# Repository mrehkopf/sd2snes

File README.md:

sd2snes
=======

SD card based multi-purpose cartridge for the SNES

See [FURiOUS's README](README.Savestates.FURiOUS.md) for information on Save States!

See [the USB protocol documentation](docs/usb-protocol.md) for the direct CDC
interface used by native clients and USB2SNES bridges.

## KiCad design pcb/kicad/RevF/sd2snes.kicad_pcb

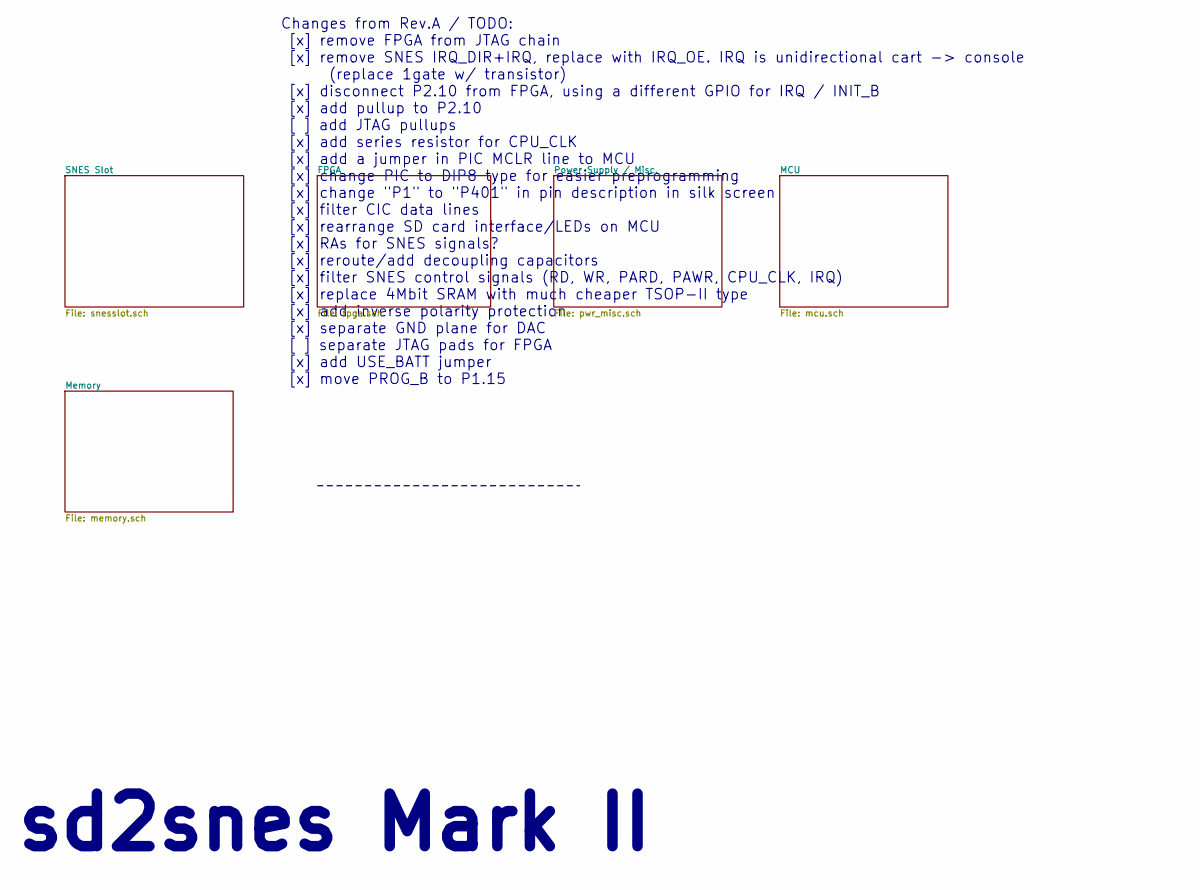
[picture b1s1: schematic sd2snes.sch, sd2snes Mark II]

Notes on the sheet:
Changes from Rev.A / TODO: [x] remove FPGA from JTAG chain [x] remove SNES IRQ_DIR+IRQ, replace with IRQ_OE. IRQ is unidirectional cart -> console (replace 1gate w/ transistor) [x] disconnect P2.10 from FPGA, using a different GPIO for IRQ / INIT_B [x] add pullup to P2.10 [ ] add JTAG pullups [x] a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
sd2snes Mark II

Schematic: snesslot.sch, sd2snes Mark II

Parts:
C101, C102, C103, C104, C105, C106, C111, C112, C113, C114, C115, C116: 100n; SM0805_FIXEDMASK
C121, C122, C123, C124, C125, C126, C127, C128: 10p; SM0805_FIXEDMASK
J101: SNESCART_EXT
Q101: 2N2222A
R101: 270; SM0805_FIXEDMASK
R102: 100k
R103: 4k7
RA101, RA102, RA105, RA106, RA107, RA108, RA109, RA110, RA111, RA112, RA113, RA114: 100
RA103, RA104: FB
U101, U102, U103: 74ALVC164245DGG; TSSOP48

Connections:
+3.3V: C101.1, C102.1, C103.1, C104.1, C105.1, C106.1, U101.31 (VCCA), U101.42 (VCCA), U102.31 (VCCA), U102.42 (VCCA), U103.31 (VCCA), U103.42 (VCCA); also elsewhere on the board
+5V: C111.1, C112.1, C113.1, C114.1, C115.1, C116.1, U101.7 (VCCB), U101.18 (VCCB), U102.7 (VCCB), U102.18 (VCCB), U103.7 (VCCB), U103.18 (VCCB); also elsewhere on the board
/SNES Slot/SNES_EXT_/IRQ: J101.18 (/IRQ), RA105.1
/SNES Slot/SNES_EXT_/PARD: J101.4 (/PARD), RA111.4
/SNES Slot/SNES_EXT_/PAWR: J101.35 (/PAWR), RA112.8
/SNES Slot/SNES_EXT_/RD: J101.23 (/RD), RA105.2
/SNES Slot/SNES_EXT_/ROMSEL: J101.49 (/ROMSEL), RA105.3
/SNES Slot/SNES_EXT_/WR: J101.54 (/WR), RA102.3
/SNES Slot/SNES_EXT_A0: J101.17 (A0), RA106.1
/SNES Slot/SNES_EXT_A1: J101.16 (A1), RA106.3
/SNES Slot/SNES_EXT_A2: J101.15 (A2), RA107.1
/SNES Slot/SNES_EXT_A3: J101.14 (A3), RA107.3
/SNES Slot/SNES_EXT_A4: J101.13 (A4), RA108.1
/SNES Slot/SNES_EXT_A5: J101.12 (A5), RA108.3
/SNES Slot/SNES_EXT_A6: J101.11 (A6), RA109.1
/SNES Slot/SNES_EXT_A7: J101.10 (A7), RA109.3
/SNES Slot/SNES_EXT_A8: J101.9 (A8), RA110.1
/SNES Slot/SNES_EXT_A9: J101.8 (A9), RA110.3
/SNES Slot/SNES_EXT_A10: J101.7 (A10), RA111.1
/SNES Slot/SNES_EXT_A11: J101.6 (A11), RA111.3
/SNES Slot/SNES_EXT_A12: J101.37 (A12), RA111.2
/SNES Slot/SNES_EXT_A13: J101.38 (A13), RA110.4
/SNES Slot/SNES_EXT_A14: J101.39 (A14), RA110.2
/SNES Slot/SNES_EXT_A15: J101.40 (A15), RA109.4
/SNES Slot/SNES_EXT_A16: J101.41 (A16), RA109.2
/SNES Slot/SNES_EXT_A17: J101.42 (A17), RA108.4
/SNES Slot/SNES_EXT_A18: J101.43 (A18), RA108.2
/SNES Slot/SNES_EXT_A19: J101.44 (A19), RA107.4
/SNES Slot/SNES_EXT_A20: J101.45 (A20), RA107.2
/SNES Slot/SNES_EXT_A21: J101.46 (A21), RA106.4
/SNES Slot/SNES_EXT_A22: J101.47 (A22), RA106.2
/SNES Slot/SNES_EXT_A23: J101.48 (A23), RA105.4
/SNES Slot/SNES_EXT_CPU_CLK: J101.57 (CPU_CLK), RA102.4
/SNES Slot/SNES_EXT_D0: J101.19 (D0), RA104.3
/SNES Slot/SNES_EXT_D1: J101.20 (D1), RA104.1
/SNES Slot/SNES_EXT_D2: J101.21 (D2), RA103.3
/SNES Slot/SNES_EXT_D3: J101.22 (D3), RA103.1
/SNES Slot/SNES_EXT_D4: J101.50 (D4), RA104.4
/SNES Slot/SNES_EXT_D5: J101.51 (D5), RA104.2
/SNES Slot/SNES_EXT_D6: J101.52 (D6), RA103.4
/SNES Slot/SNES_EXT_D7: J101.53 (D7), RA103.2
/SNES Slot/SNES_EXT_PA0: J101.28 (PA0), RA102.1
/SNES Slot/SNES_EXT_PA1: J101.59 (PA1), RA102.2
/SNES Slot/SNES_EXT_PA2: J101.29 (PA2), RA101.3
/SNES Slot/SNES_EXT_PA3: J101.60 (PA3), RA101.4
/SNES Slot/SNES_EXT_PA4: J101.30 (PA4), RA101.1
/SNES Slot/SNES_EXT_PA5: J101.61 (PA5), RA101.2
/SNES Slot/SNES_EXT_PA6: J101.3 (PA6), RA112.7
/SNES Slot/SNES_EXT_PA7: J101.34 (PA7), RA112.6
/SNES Slot/SNES_EXT_REFRESH: C126.1, J101.33 (REFRESH), RA112.5
/SNES Slot/SNES_EXT_SYS_CLK: J101.1 (SYS_CLK), R101.2, U103.23 (2B7)
AUDIO_L: J101.31 (LINE_L); also elsewhere on the board
AUDIO_R: J101.62 (LINE_R); also elsewhere on the board
CIC_CLK: J101.56 (CIC_P6_CLK); also elsewhere on the board
CIC_RESET: J101.25 (CIC_P7_RESET); also elsewhere on the board
DATABUS_/OE: U101.25 (2/OE); also elsewhere on the board
DATABUS_DIR: U101.24 (2DIR); also elsewhere on the board
EXT_CIC_DATA0: J101.55 (CIC_P2_DIN); also elsewhere on the board
EXT_CIC_DATA1: J101.24 (CIC_P1_DOUT); also elsewhere on the board
GND: C101.2, C102.2, C103.2, C104.2, C105.2, C106.2, C111.2, C112.2, C113.2, C114.2, C115.2, C116.2, C121.2, C122.2, C123.2, C124.2, C125.2, C126.2, C127.2, C128.2, J101.5 (GND), J101.36 (GND), Q101.1 (E), R101.1, R102.2, U101.1 (1DIR), U101.4 (GND), U101.10 (GND), U101.15 (GND), U101.21 (GND), U101.28 (GND), U101.34 (GND), U101.39 (GND), U101.45 (GND), U101.48 (1/OE), U102.1 (1DIR), U102.4 (GND), U102.10 (GND), U102.15 (GND), U102.21 (GND), U102.24 (2DIR), U102.25 (2/OE), U102.28 (GND), U102.34 (GND), U102.39 (GND), U102.45 (GND), U102.48 (1/OE), U103.1 (1DIR), U103.4 (GND), U103.10 (GND), U103.15 (GND), U103.21 (GND), U103.24 (2DIR), U103.25 (2/OE), U103.28 (GND), U103.34 (GND), U103.39 (GND), U103.45 (GND), U103.48 (1/OE); also elsewhere on the board
unnamed: C125.1, RA105.7, U102.2 (1B0)
unnamed: C124.1, RA102.6, U101.11 (1B6)
unnamed: Q101.2 (B), R102.1, R103.2
unnamed: RA108.5, U102.22 (2B6)
unnamed: RA105.5, U102.5 (1B2)
unnamed: RA106.8, U102.6 (1B3)
unnamed: RA106.7, U102.8 (1B4)
unnamed: RA106.6, U102.9 (1B5)
unnamed: RA108.6, U102.20 (2B5)
unnamed: RA106.5, U102.11 (1B6)
unnamed: RA107.8, U102.12 (1B7)
unnamed: RA107.7, U102.13 (2B0)
unnamed: RA109.8, U102.23 (2B7)
unnamed: RA107.6, U102.14 (2B1)
unnamed: RA107.5, U102.16 (2B2)
unnamed: RA103.6, U101.16 (2B2)
unnamed: RA104.6, U101.22 (2B6)
unnamed: RA113.4, U101.32 (2A3)
unnamed: RA103.8, U101.13 (2B0)
unnamed: RA104.5, U101.23 (2B7)
unnamed: RA113.3, U101.33 (2A2)
unnamed: RA103.7, U101.14 (2B1)
unnamed: RA113.2, U101.35 (2A1)
unnamed: RA114.4, U101.26 (2A7)
unnamed: RA113.1, U101.36 (2A0)
unnamed: RA103.5, U101.17 (2B3)
unnamed: RA114.3, U101.27 (2A6)
unnamed: RA104.8, U101.19 (2B4)
unnamed: RA101.7, U101.3 (1B1)
unnamed: RA108.8, U102.17 (2B3)
unnamed: RA108.7, U102.19 (2B4)
unnamed: RA101.8, U101.2 (1B0)
unnamed: RA101.6, U101.5 (1B2)
unnamed: RA101.5, U101.6 (1B3)
unnamed: RA102.8, U101.8 (1B4)
unnamed: RA102.7, U101.9 (1B5)
unnamed: RA104.7, U101.20 (2B5)
unnamed: RA114.1, U101.30 (2A4)
unnamed: RA109.6, U103.3 (1B1)
unnamed: RA109.7, U103.2 (1B0)
unnamed: RA109.5, U103.5 (1B2)
unnamed: RA110.8, U103.6 (1B3)
unnamed: C122.1, RA105.6, U102.3 (1B1)
unnamed: C121.1, RA102.5, U101.12 (1B7)
unnamed: RA110.7, U103.8 (1B4)
unnamed: RA114.2, U101.29 (2A5)
unnamed: RA111.8, U103.12 (1B7)
unnamed: C123.1, Q101.3 (C), RA105.8
unnamed: C127.1, RA112.1, U103.17 (2B3)
unnamed: RA112.2, U103.19 (2B4)
unnamed: RA112.3, U103.20 (2B5)
unnamed: RA112.4, U103.22 (2B6)
unnamed: C128.1, RA111.5, U103.16 (2B2)
unnamed: RA111.6, U103.14 (2B1)
unnamed: RA111.7, U103.13 (2B0)
unnamed: RA110.5, U103.11 (1B6)
unnamed: RA110.6, U103.9 (1B5)
SNES_/PARD: U103.33 (2A2); also elsewhere on the board
SNES_/PAWR: U103.32 (2A3); also elsewhere on the board
SNES_/RD: U102.47 (1A0); also elsewhere on the board
SNES_/RESET: J101.26 (/RESET); also elsewhere on the board
SNES_/ROMSEL: U102.46 (1A1); also elsewhere on the board
SNES_/WR: U101.38 (1A6); also elsewhere on the board
SNES_A0: U102.43 (1A3); also elsewhere on the board
SNES_A1: U102.40 (1A5); also elsewhere on the board
SNES_A2: U102.37 (1A7); also elsewhere on the board
SNES_A3: U102.35 (2A1); also elsewhere on the board
SNES_A4: U102.32 (2A3); also elsewhere on the board
SNES_A5: U102.29 (2A5); also elsewhere on the board
SNES_A6: U102.26 (2A7); also elsewhere on the board
SNES_A7: U103.46 (1A1); also elsewhere on the board
SNES_A8: U103.43 (1A3); also elsewhere on the board
SNES_A9: U103.40 (1A5); also elsewhere on the board
SNES_A10: U103.37 (1A7); also elsewhere on the board
SNES_A11: U103.35 (2A1); also elsewhere on the board
SNES_A12: U103.36 (2A0); also elsewhere on the board
SNES_A13: U103.38 (1A6); also elsewhere on the board
SNES_A14: U103.41 (1A4); also elsewhere on the board
SNES_A15: U103.44 (1A2); also elsewhere on the board
SNES_A16: U103.47 (1A0); also elsewhere on the board
SNES_A17: U102.27 (2A6); also elsewhere on the board
SNES_A18: U102.30 (2A4); also elsewhere on the board
SNES_A19: U102.33 (2A2); also elsewhere on the board
SNES_A20: U102.36 (2A0); also elsewhere on the board
SNES_A21: U102.38 (1A6); also elsewhere on the board
SNES_A22: U102.41 (1A4); also elsewhere on the board
SNES_A23: U102.44 (1A2); also elsewhere on the board
SNES_CPU_CLK: U101.37 (1A7); also elsewhere on the board
SNES_D0: RA114.6; also elsewhere on the board
SNES_D1: RA114.8; also elsewhere on the board
SNES_D2: RA113.6; also elsewhere on the board
SNES_D3: RA113.8; also elsewhere on the board
SNES_D4: RA114.5; also elsewhere on the board
SNES_D5: RA114.7; also elsewhere on the board
SNES_D6: RA113.5; also elsewhere on the board
SNES_D7: RA113.7; also elsewhere on the board
SNES_IRQ_EN: R103.1; also elsewhere on the board
SNES_PA0: U101.41 (1A4); also elsewhere on the board
SNES_PA1: U101.40 (1A5); also elsewhere on the board
SNES_PA2: U101.44 (1A2); also elsewhere on the board
SNES_PA3: U101.43 (1A3); also elsewhere on the board
SNES_PA4: U101.47 (1A0); also elsewhere on the board
SNES_PA5: U101.46 (1A1); also elsewhere on the board
SNES_PA6: U103.30 (2A4); also elsewhere on the board
SNES_PA7: U103.29 (2A5); also elsewhere on the board
SNES_REFRESH: U103.27 (2A6); also elsewhere on the board
SNES_SYS_CLK: U103.26 (2A7); also elsewhere on the board

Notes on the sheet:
SNES bus, level shift

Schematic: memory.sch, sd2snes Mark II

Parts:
C501, C502, C511: 100n; SM0805_FIXEDMASK
D511: BAT54C; SOT23EBC
Q511: 2N2222A; SOT23EBC
R511: 20k; SM0805_FIXEDMASK
R512: 4k7; SM0805_FIXEDMASK
R513: 100k; SM0805_FIXEDMASK
U501: MT45W8MW16; VFBGA54
U511: CY62148EV30-ZSXI

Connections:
+1.8V: C502.1, U501.D6 (Vcc); also elsewhere on the board
+3.3V: C501.1, D511.1 (Anode), R512.2, U501.E1 (VccQ); also elsewhere on the board
+BATT: D511.2 (cathode); also elsewhere on the board
/Memory/RAM_/CE: Q511.3 (C), R511.2, U511.22
/Memory/SRAM_Vcc: C511.1, D511.3 (AK), R511.1, U511.32
GND: C501.2, C502.2, C511.2, Q511.1 (E), R513.2, U501.A6 (CRE), U501.D1 (VssQ), U501.E6 (Vss), U501.J2 (CLK), U501.J3 (/ADV), U511.16; also elsewhere on the board
unnamed: Q511.2 (B), R512.1, R513.1
RAM_/OE: U511.24; also elsewhere on the board
RAM_/WE: U511.29; also elsewhere on the board
RAM_A0: U511.12; also elsewhere on the board
RAM_A1: U511.11; also elsewhere on the board
RAM_A2: U511.10; also elsewhere on the board
RAM_A3: U511.9; also elsewhere on the board
RAM_A4: U511.8; also elsewhere on the board
RAM_A5: U511.7; also elsewhere on the board
RAM_A6: U511.6; also elsewhere on the board
RAM_A7: U511.5; also elsewhere on the board
RAM_A8: U511.27; also elsewhere on the board
RAM_A9: U511.26; also elsewhere on the board
RAM_A10: U511.23; also elsewhere on the board
RAM_A11: U511.25; also elsewhere on the board
RAM_A12: U511.4; also elsewhere on the board
RAM_A13: U511.28; also elsewhere on the board
RAM_A14: U511.3; also elsewhere on the board
RAM_A15: U511.31; also elsewhere on the board
RAM_A16: U511.2; also elsewhere on the board
RAM_A17: U511.1; also elsewhere on the board
RAM_A18: U511.30; also elsewhere on the board
RAM_DQ0: U511.13; also elsewhere on the board
RAM_DQ1: U511.14; also elsewhere on the board
RAM_DQ2: U511.15; also elsewhere on the board
RAM_DQ3: U511.17; also elsewhere on the board
RAM_DQ4: U511.18; also elsewhere on the board
RAM_DQ5: U511.19; also elsewhere on the board
RAM_DQ6: U511.20; also elsewhere on the board
RAM_DQ7: U511.21; also elsewhere on the board
ROM_/CE: U501.B5 (/CE); also elsewhere on the board
ROM_/LB: U501.A1 (/LB); also elsewhere on the board
ROM_/OE: U501.A2 (/OE); also elsewhere on the board
ROM_/UB: U501.B2 (/UB); also elsewhere on the board
ROM_/WE: U501.G5 (/WE); also elsewhere on the board
ROM_A0: U501.A3 (A0); also elsewhere on the board
ROM_A1: U501.A4 (A1); also elsewhere on the board
ROM_A2: U501.A5 (A2); also elsewhere on the board
ROM_A3: U501.B3 (A3); also elsewhere on the board
ROM_A4: U501.B4 (A4); also elsewhere on the board
ROM_A5: U501.C3 (A5); also elsewhere on the board
ROM_A6: U501.C4 (A6); also elsewhere on the board
ROM_A7: U501.D4 (A7); also elsewhere on the board
ROM_A8: U501.H2 (A8); also elsewhere on the board
ROM_A9: U501.H3 (A9); also elsewhere on the board
ROM_A10: U501.H4 (A10); also elsewhere on the board
ROM_A11: U501.H5 (A11); also elsewhere on the board
ROM_A12: U501.G3 (A12); also elsewhere on the board
ROM_A13: U501.G4 (A13); also elsewhere on the board
ROM_A14: U501.F3 (A14); also elsewhere on the board
ROM_A15: U501.F4 (A15); also elsewhere on the board
ROM_A16: U501.E4 (A16); also elsewhere on the board
ROM_A17: U501.D3 (A17); also elsewhere on the board
ROM_A18: U501.H1 (A18); also elsewhere on the board
ROM_A19: U501.G2 (A19); also elsewhere on the board
ROM_A20: U501.H6 (A20); also elsewhere on the board
ROM_A21: U501.E3 (A21); also elsewhere on the board
ROM_A22: U501.J4 (A22); also elsewhere on the board
ROM_DQ0: U501.B6 (DQ0); also elsewhere on the board
ROM_DQ1: U501.C5 (DQ1); also elsewhere on the board
ROM_DQ2: U501.C6 (DQ2); also elsewhere on the board
ROM_DQ3: U501.D5 (DQ3); also elsewhere on the board
ROM_DQ4: U501.E5 (DQ4); also elsewhere on the board
ROM_DQ5: U501.F5 (DQ5); also elsewhere on the board
ROM_DQ6: U501.F6 (DQ6); also elsewhere on the board
ROM_DQ7: U501.G6 (DQ7); also elsewhere on the board
ROM_DQ8: U501.B1 (DQ8); also elsewhere on the board
ROM_DQ9: U501.C1 (DQ9); also elsewhere on the board
ROM_DQ10: U501.C2 (DQ10); also elsewhere on the board
ROM_DQ11: U501.D2 (DQ11); also elsewhere on the board
ROM_DQ12: U501.E2 (DQ12); also elsewhere on the board
ROM_DQ13: U501.F2 (DQ13); also elsewhere on the board
ROM_DQ14: U501.F1 (DQ14); also elsewhere on the board
ROM_DQ15: U501.G1 (DQ15); also elsewhere on the board

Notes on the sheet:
Memory
SRAM battery power
Battery power OE switch
4Mbits 45ns SRAM (battery RAM + custom chip work RAM)
128Mbits 70ns PSRAM (ROM area)

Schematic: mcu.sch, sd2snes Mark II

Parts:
C401, C402, C403, C404, C405, C412: 100n; SM0805_FIXEDMASK
C406, C407: 33p; SM0805_FIXEDMASK
C408, C409: 10p; SM0805_FIXEDMASK
C411: 10u; SM0805_FIXEDMASK
D401: LED 2mA 1.9V, green; LED-3MM-FIXED
D402: LED 2mA 1.8V, yellow; LED-3MM-FIXED
D403: LED 2mA 1.7V, red; LED-3MM-FIXED
J411: Hirose DM1AA
J421: USB Mini-B SMT; USB-MINIB-THT
JP401, JP402: JUMPER
P401: CONN_7X2; pin_array_7x2
P402, P403: CONN_2; PIN_ARRAY_2X1
P404: CONN_3X2
R401, R402, R403: 680; SM0805_FIXEDMASK
R404, R407: 10k; SM0805_FIXEDMASK
R405, R406: 100; SM0805_FIXEDMASK
R421, R422: 33; SM0805_FIXEDMASK
R423: 1.5k; SM0805_FIXEDMASK
U401: LPC1754; LQFP80-.5
X401: 12MHz; XTAL_SMD_05032
X402: 32.768kHz; XTAL_SMD_05019

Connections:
+3.3V: C401.1, C402.1, C403.1, C404.1, C411.1, C412.1, D401.1 (A), D402.1 (A), D403.1 (A), J411.4 (VDD), P401.1, R404.2, R407.2, U401.8 (VDDA), U401.10 (VREFP), U401.21 (VDD), U401.34 (VDD(REG)), U401.42 (VDD), U401.56 (VDD), U401.67 (VDD(REG)), U401.77 (VDD); also elsewhere on the board
+5V: P401.2; also elsewhere on the board
+BATT: U401.16 (VBAT); also elsewhere on the board
/RESET: C405.1, P401.5, P402.2 (PM), R404.1, U401.14 (/RESET)
/TRST: P401.9, U401.4 (/TRST)
/USEBATT: JP402.2, U401.70 (P1[14])
CCLK: R405.1; also elsewhere on the board
CIC_DATA0: U401.38 (P0[1]/TD1/RXD3/SCL1); also elsewhere on the board
CIC_DATA1: U401.37 (P0[0]/RD1/TXD3/SDA1); also elsewhere on the board
CIC_MCLR: JP401.2; also elsewhere on the board
CIC_STATUS: U401.36 (MCOB2/PCAP1[1]/MAT0[1]/P1[29]); also elsewhere on the board
DAC_/DEM: U401.30 (P1[24]/MCI2/PWM1[5]/MOSI0); also elsewhere on the board
DIN+MCU_/OVR: U401.50 (TXD2/P2[8]); also elsewhere on the board
DONE: U401.44 (P0[22]/RTS1/TD1); also elsewhere on the board
EXT_TDI: P401.11, U401.2 (TDI)
EXT_TDO: P401.12, U401.1 (TDO/SWO)
FPGA_CLK: U401.39 (P0[10]/TXD2/SDA2/MAT3[0]); also elsewhere on the board
GND: C401.2, C402.2, C403.2, C404.2, C405.2, C406.2, C407.2, C408.2, C409.2, C411.2, C412.2, J411.3 (VSS), J411.6 (VSS2), J411.GND1, J411.GND2, J421.5 (GND), J421.6 (Shield1), J421.7 (Shield2), JP402.1, P401.3, P402.1, P403.1, U401.9 (VSSA), U401.12 (VREFN), U401.24 (VSS), U401.33 (VSS), U401.43 (VSS), U401.57 (VSS), U401.66 (VSS), U401.78 (VSS); also elsewhere on the board
INIT_B+MCU_IRQ: U401.49 (USB_CONNECT/RXD2/P2[9]); also elsewhere on the board
MCU_SPARE: P404.4, U401.73 (P1[8])
MCU_SPI_MISO: U401.46 (P0[17]/CTS1/MISO0/MISO); also elsewhere on the board
MCU_SPI_MOSI: U401.45 (P0[18]/DCD1/MOSI0/MOSI); also elsewhere on the board
MCU_SPI_SCK: U401.47 (P0[15]/TXD1/SCK0/SCK); also elsewhere on the board
MCU_SPI_SS: U401.48 (P0[16]/RXD1/SSEL0/SSEL); also elsewhere on the board
unnamed: J411.WP (WPROT), U401.64 (P0[6]/SSEL1/MAT2[0])
unnamed: R401.1, U401.54 (PWM1[5]/DSR1/TRACEDATA[1]/P2[4])
unnamed: JP401.1, U401.31 (P1[25]/MCOA1/MAT1[1])
unnamed: D402.2 (K), R402.2
unnamed: R421.2, U401.22 (P0[29]/USB_D+)
unnamed: J421.2 (D-), R422.1
unnamed: D403.2 (K), R403.2
unnamed: P403.2 (PM), U401.25 (P1[18]/USB_UP_LED/PWM1[1]/CAP1[0])
unnamed: R422.2, U401.23 (P0[30]/USB_D-)
unnamed: J421.3 (D+), R421.1, R423.1
unnamed: D401.2 (K), R401.2
unnamed: J411.DT (DETECT), U401.62 (P0[8]/MISO1/MAT2[2])
unnamed: R402.1, U401.53 (PWM1[6]/DTR1/TRACEDATA[0]/P2[5])
unnamed: R403.1, U401.29 (P1[23]/MCI1/PWM1[4]/MISO0)
unnamed: R406.1, U401.69 (P1[15])
unnamed: R405.2, U401.40 (P0[11]/RXD2/SCL2/MAT3[1])
unnamed: J421.1 (VBUS), U401.18 (V_BUS/AD0[4]/P1[30])
unnamed: C408.1, U401.13 (RTCX1), X402.1
unnamed: C409.1, U401.15 (RTCX2), X402.2
unnamed: C406.1, U401.19 (XTAL1), X401.1
unnamed: C407.1, U401.20 (XTAL2), X401.2
P1_CLK: P404.2, U401.75 (P1[1])
P1_D0: P404.1, U401.76 (P1[0])
P2.10: P401.4, R407.1, U401.41 (/EINT0/NMI/P2[10])
P2_CLK: P404.5, U401.72 (P1[9])
P2_D0: P404.6, U401.71 (P1[10])
PROG_B: R406.2; also elsewhere on the board
P_LATCH: P404.3, U401.74 (P1[4])
RX0: P401.13, U401.80 (P0[3]/RXD0/AD0[6])
RX3: P401.7, U401.6 (P0[26]/AD0[3]/AOUT/RXD3)
SD_CLK: J411.5 (SCLK), U401.63 (P0[7]/SCK1/MAT2[1]); also elsewhere on the board
SD_CMD: J411.2 (DI), U401.61 (P0[9]/MOSI1/MAT2[3]); also elsewhere on the board
SD_DAT0: J411.7 (DO), U401.60 (PWM1[1]/TXD1/P2[0]); also elsewhere on the board
SD_DAT1: J411.8 (DAT1), U401.59 (PWM1[2]/RXD1/P2[1]); also elsewhere on the board
SD_DAT2: J411.9 (DAT2), U401.58 (PWM1[3]/CTS1/TRACEDATA[3]/P2[2]); also elsewhere on the board
SD_DAT3: J411.1 (CS), U401.55 (PWM1[4]/DCD1/TRACEDATA[2]/P2[3]); also elsewhere on the board
SNES_/RESET: U401.32 (MCOB1/PWM1[6]/CAP0[0]/P1[26]); also elsewhere on the board
TCK: P401.8, U401.5 (TCK/SWDCLK)
TMS: P401.10, U401.3 (TMS/SWDIO)
TX0: P401.14, U401.79 (P0[2]/TXD0/AD0[7])
TX3: P401.6, U401.7 (P0[25]/AD0[2]/TXD3)
USB_SWCONN: R423.2, U401.65 (RX_MCLK/MAT2[0]/TXD3/P4[28])

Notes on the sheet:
open in case of in-circuit PIC programming
or 3000mcd LEDs (10k for R401-403)
Freeze button
MCU, SD, debug
Reset button
2mA low current LEDs

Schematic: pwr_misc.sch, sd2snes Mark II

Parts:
BT351: Keystone 1059 / KZH20PCB; BT_KEYSTONE_1059_20MM
C301, C303, C304, C311, C312, C321, C322: 4.7u; SM0805_FIXEDMASK
C302, C347, C349: 10n; SM0805_FIXEDMASK
C331, C341, C343: 100n; SM0805_FIXEDMASK
C332, C333: 100p; SM0805_FIXEDMASK
C342: 1u; SM0805_FIXEDMASK
C344, C345: 10u; SM0805_FIXEDMASK
C346, C348: 3.3u; SM0805_FIXEDMASK
C391: 100u
FB341: FILTER
JP341: FB 0603
L301, L302: 1uH; SM1210L; PartNo LQH32PN1R0NN0L
L391: 10uH
Q301: IRLML6402PbF
R301: 20k; SM0805_FIXEDMASK
R331, R332, R333: 680; SM0805_FIXEDMASK
R341, R343: 470; SM0805_FIXEDMASK
R342, R344: 10k; SM0805_FIXEDMASK
U301: MIC23250-S4YMT; QFN10-2x2
U311: MCP1824-1802E/OT; SOT23-5
U321: MCP1824-2502E/OT; SOT23-5
U331: PIC12F629-I/P; SO8N
U341: CS4344; TSSOP10

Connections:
+1.2V: C303.1, L301.1, U301.1 (SNS1); also elsewhere on the board
+1.8V: C312.1, U311.5 (Vout); also elsewhere on the board
+2.5V: C322.1, U321.5 (Vout); also elsewhere on the board
+3.3V: C304.1, C311.1, C321.1, FB341.1, L302.2, U301.10 (SNS2), U311.1 (Vin), U311.3 (/SHDN), U321.1 (Vin), U321.3 (/SHDN); also elsewhere on the board
+5V: C301.1, C302.1, C331.1, Q301.S, U301.2 (EN1), U301.6 (VIN), U301.8 (AVIN), U301.9 (EN2), U331.1 (VDD); also elsewhere on the board
+BATT: BT351.1 (+); also elsewhere on the board
/Power Supply / Misc./REG_SW1: L301.2, U301.4 (SW1)
/Power Supply / Misc./REG_SW2: L302.1, U301.7 (SW2)
AUDIO_L: C349.1, R343.1; also elsewhere on the board
AUDIO_R: C347.1, R341.1; also elsewhere on the board
CIC_CLK: R331.2; also elsewhere on the board
CIC_DATA0: C332.1, R332.1, U331.7 (GP0); also elsewhere on the board
CIC_DATA1: C333.1, R333.2, U331.6 (GP1); also elsewhere on the board
CIC_MCLR: U331.4 (GP3/MCLR); also elsewhere on the board
CIC_RESET: U331.5 (GP2); also elsewhere on the board
CIC_STATUS: U331.3 (GP4/OSC2); also elsewhere on the board
DAC_/DEM: U341.2 (/DEM/SCLK); also elsewhere on the board
DAC_LRCK: U341.3 (LRCK); also elsewhere on the board
DAC_MCLK: U341.4 (MCLK); also elsewhere on the board
DAC_SDIN: U341.1 (SDIN); also elsewhere on the board
EXT_CIC_DATA0: R332.2; also elsewhere on the board
EXT_CIC_DATA1: R333.1; also elsewhere on the board
GND: BT351.2 (-), C301.2, C302.2, C303.2, C304.2, C311.2, C312.2, C321.2, C322.2, C331.2, C332.2, C333.2, C391.2, JP341.1, R301.1, U301.3 (AGND), U301.5 (PGND), U311.2 (GND), U321.2 (GND), U331.8 (VSS); also elsewhere on the board
unnamed: L391.2, Q301.D
unnamed: Q301.G, R301.2
unnamed: R331.1, U331.2 (GP5/OSC1)
unnamed: C346.2, U341.10 (AOUTR)
unnamed: C343.1, C344.1, U341.5 (VQ)
unnamed: C345.1, U341.6 (FILT)
unnamed: C348.2, U341.7 (AOUTL)
unnamed: C348.1, R343.2, R344.1
unnamed: C346.1, R341.2, R342.1

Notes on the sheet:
Stuff with 0603 ferrite bead
Power, DAC, CIC, Batt
inverse polarity protection
Battery (SRAM + RTC)
2.5V LDO
1.8V LDO
3.3V + 1.2V Step-Down
Audio DAC
Power Supply
SuperCIC Key

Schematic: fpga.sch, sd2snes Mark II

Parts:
C201, C202, C203, C204, C205, C206, C207, C208, C209, C210, C211, C212, C213, C214, C215, C221, C222, C223, C224, C231, C232, C233, C234: 100n; SM0805_FIXEDMASK
P113: CONN_1
U201: XC3S400-PQ208; PQFP208

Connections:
+1.2V: C221.1, C222.1, C223.1, C224.1, U201.70 (VCCINT), U201.88 (VCCINT), U201.174 (VCCINT), U201.192 (VCCINT); also elsewhere on the board
+2.5V: C210.1, C211.1, C212.1, C213.1, C214.1, C215.1, U201.17 (VCCAUX), U201.38 (VCCAUX), U201.69 (VCCAUX), U201.89 (VCCAUX), U201.121 (VCCAUX), U201.142 (VCCAUX), U201.173 (VCCAUX), U201.193 (VCCAUX); also elsewhere on the board
+3.3V: C201.1, C202.1, C203.1, C204.1, C205.1, C206.1, C207.1, C208.1, C209.1, C231.1, C232.1, C233.1, C234.1, U201.6 (VCCO_7), U201.23 (VCCO_7), U201.32 (VCCO_6), U201.49 (VCCO_6), U201.60 (VCCO_5), U201.73 (VCCO_5), U201.84 (VCCO_4), U201.98 (VCCO_4), U201.110 (VCCO_3), U201.127 (VCCO_3), U201.136 (VCCO_2), U201.153 (VCCO_2), U201.164 (VCCO_1), U201.177 (VCCO_1), U201.188 (VCCO_0), U201.201 (VCCO_0); also elsewhere on the board
CCLK: U201.104 (CCLK); also elsewhere on the board
DAC_LRCK: U201.77 (IO_L32N_5/GCLK3); also elsewhere on the board
DAC_MCLK: U201.76 (IO_L32P_5/GCLK2); also elsewhere on the board
DAC_SDIN: U201.78 (IO/VREF_5); also elsewhere on the board
DATABUS_/OE: U201.109 (IO_L17N_3); also elsewhere on the board
DATABUS_DIR: U201.111 (IO_L19P_3); also elsewhere on the board
DIN+MCU_/OVR: U201.92 (IO_L27N_4/DIN/D0); also elsewhere on the board
DONE: U201.103 (DONE); also elsewhere on the board
FPGA_CLK: U201.80 (IO_L32N_4/GCLK1); also elsewhere on the board
GND: C201.2, C202.2, C203.2, C204.2, C205.2, C206.2, C207.2, C208.2, C209.2, C210.2, C211.2, C212.2, C213.2, C214.2, C215.2, C221.2, C222.2, C223.2, C224.2, C231.2, C232.2, C233.2, C234.2, U201.1 (GND), U201.8 (GND), U201.14 (GND), U201.25 (GND), U201.30 (GND), U201.41 (GND), U201.47 (GND), U201.53 (GND), U201.59 (GND), U201.66 (GND), U201.75 (GND), U201.82 (GND), U201.91 (GND), U201.99 (GND), U201.105 (GND), U201.112 (GND), U201.118 (GND), U201.129 (GND), U201.134 (GND), U201.145 (GND), U201.151 (GND), U201.157 (GND), U201.163 (GND), U201.170 (GND), U201.179 (GND), U201.186 (GND), U201.195 (GND), U201.202 (GND), U201.206 (HSWAP_EN); also elsewhere on the board
INIT_B+MCU_IRQ: U201.83 (IO_L31N_4/INIT_B); also elsewhere on the board
MCU_SPI_MISO: U201.72 (IO_L31P_5/D5); also elsewhere on the board
MCU_SPI_MOSI: U201.74 (IO_L31N_5/D4); also elsewhere on the board
MCU_SPI_SCK: U201.71 (IO); also elsewhere on the board
MCU_SPI_SS: U201.68 (IO_L28N_5/D6); also elsewhere on the board
unnamed: P113.1, U201.113 (IO_L19N_3)
PROG_B: U201.207 (PROG_B); also elsewhere on the board
RAM_/OE: U201.36 (IO_L23P_6); also elsewhere on the board
RAM_/WE: U201.50 (IO/VREF_6); also elsewhere on the board
RAM_A0: U201.28 (IO_L40P_6/VREF_6); also elsewhere on the board
RAM_A1: U201.31 (IO_L39P_6); also elsewhere on the board
RAM_A2: U201.33 (IO_L39N_6); also elsewhere on the board
RAM_A3: U201.35 (IO_L24N_6/VREF_6); also elsewhere on the board
RAM_A4: U201.37 (IO_L23N_6); also elsewhere on the board
RAM_A5: U201.40 (IO_L22N_6); also elsewhere on the board
RAM_A6: U201.43 (IO_L21N_6); also elsewhere on the board
RAM_A7: U201.45 (IO_L20N_6); also elsewhere on the board
RAM_A8: U201.44 (IO_L20P_6); also elsewhere on the board
RAM_A9: U201.42 (IO_L21P_6); also elsewhere on the board
RAM_A10: U201.34 (IO_L24P_6); also elsewhere on the board
RAM_A11: U201.39 (IO_L22P_6); also elsewhere on the board
RAM_A12: U201.48 (IO_L19N_6); also elsewhere on the board
RAM_A13: U201.46 (IO_L19P_6); also elsewhere on the board
RAM_A14: U201.51 (IO_L01P_6/VRN_6); also elsewhere on the board
RAM_A15: U201.58 (IO_L01N_5/RDWR_B); also elsewhere on the board
RAM_A16: U201.57 (IO_L01P_5/CS_B); also elsewhere on the board
RAM_A17: U201.61 (IO_L10P_5/VRN_5); also elsewhere on the board
RAM_A18: U201.52 (IO_L01N_6/VRP_6); also elsewhere on the board
RAM_DQ0: U201.26 (IO_L40P_7); also elsewhere on the board
RAM_DQ1: U201.22 (IO_L39P_7); also elsewhere on the board
RAM_DQ2: U201.20 (IO_L24P_7); also elsewhere on the board
RAM_DQ3: U201.19 (IO_L23N_7); also elsewhere on the board
RAM_DQ4: U201.21 (IO_L24N_7); also elsewhere on the board
RAM_DQ5: U201.24 (IO_L39N_7); also elsewhere on the board
RAM_DQ6: U201.27 (IO_L40N_7/VREF_7); also elsewhere on the board
RAM_DQ7: U201.29 (IO_L40N_6); also elsewhere on the board
ROM_/CE: U201.172 (IO_L28N_1); also elsewhere on the board
ROM_/LB: U201.156 (IO_L01N_2/VRP_2); also elsewhere on the board
ROM_/OE: U201.162 (IO_L01N_1/VRP_1); also elsewhere on the board
ROM_/UB: U201.161 (IO_L01P_1/VRN_1); also elsewhere on the board
ROM_/WE: U201.190 (IO_L30P_0); also elsewhere on the board
ROM_A0: U201.166 (IO_L10N_1/VREF_1); also elsewhere on the board
ROM_A1: U201.168 (IO_L27P_1); also elsewhere on the board
ROM_A2: U201.171 (IO_L28P_1); also elsewhere on the board
ROM_A3: U201.165 (IO_L10P_1); also elsewhere on the board
ROM_A4: U201.169 (IO_L27N_1); also elsewhere on the board
ROM_A5: U201.18 (IO_L23P_7); also elsewhere on the board
ROM_A6: U201.175 (IO); also elsewhere on the board
ROM_A7: U201.167 (IO); also elsewhere on the board
ROM_A8: U201.205 (IO/VREF_0); also elsewhere on the board
ROM_A9: U201.204 (IO_L01N_0/VRP_0); also elsewhere on the board
ROM_A10: U201.197 (IO); also elsewhere on the board
ROM_A11: U201.196 (IO_L27N_0); also elsewhere on the board
ROM_A12: U201.2 (IO_L01P_7/VRN_7); also elsewhere on the board
ROM_A13: U201.194 (IO_L27P_0); also elsewhere on the board
ROM_A14: U201.200 (IO/VREF_0); also elsewhere on the board
ROM_A15: U201.184 (IO_L32N_0/GCLK7); also elsewhere on the board
ROM_A16: U201.199 (IO_L25N_0); also elsewhere on the board
ROM_A17: U201.11 (IO_L20N_7); also elsewhere on the board
ROM_A18: U201.3 (IO_L01N_7/VRP_7); also elsewhere on the board
ROM_A19: U201.4 (IO_L16P_7/VREF_7); also elsewhere on the board
ROM_A20: U201.191 (IO_L30N_0); also elsewhere on the board
ROM_A21: U201.203 (IO_L01P_0/VRN_0); also elsewhere on the board
ROM_A22: U201.198 (IO_L25P_0); also elsewhere on the board
ROM_DQ0: U201.176 (IO_L31P_1); also elsewhere on the board
ROM_DQ1: U201.178 (IO_L31N_1/VREF_1); also elsewhere on the board
ROM_DQ2: U201.181 (IO_L32N_1GCLK5); also elsewhere on the board
ROM_DQ3: U201.182 (IO); also elsewhere on the board
ROM_DQ4: U201.183 (IO_L32P_0/GCLK6); also elsewhere on the board
ROM_DQ5: U201.187 (IO_L31N_0); also elsewhere on the board
ROM_DQ6: U201.185 (IO_L31P_0/VREF_0); also elsewhere on the board
ROM_DQ7: U201.189 (IO); also elsewhere on the board
ROM_DQ8: U201.16 (IO_L22N_7); also elsewhere on the board
ROM_DQ9: U201.13 (IO_L21N_7); also elsewhere on the board
ROM_DQ10: U201.15 (IO_L22P_7); also elsewhere on the board
ROM_DQ11: U201.12 (IO_L21P_7); also elsewhere on the board
ROM_DQ12: U201.10 (IO_L20P_7); also elsewhere on the board
ROM_DQ13: U201.7 (IO_L19P_7); also elsewhere on the board
ROM_DQ14: U201.9 (IO_L19N_7/VREF_7); also elsewhere on the board
ROM_DQ15: U201.5 (IO_L16N_7); also elsewhere on the board
SD_CLK: U201.64 (IO_L27P_5); also elsewhere on the board
SD_CMD: U201.67 (IO_L28P_5/D7); also elsewhere on the board
SD_DAT0: U201.65 (IO_L27N_5/VREF_5); also elsewhere on the board
SD_DAT1: U201.79 (IO_L32P_4/GCLK0); also elsewhere on the board
SD_DAT2: U201.62 (IO_L10N_5/VRP_5); also elsewhere on the board
SD_DAT3: U201.63 (IO); also elsewhere on the board
SNES_/PARD: U201.149 (IO_L20N_2); also elsewhere on the board
SNES_/PAWR: U201.150 (IO_L19P_2); also elsewhere on the board
SNES_/RD: U201.115 (IO_L20N_3); also elsewhere on the board
SNES_/ROMSEL: U201.116 (IO_L21P_3); also elsewhere on the board
SNES_/WR: U201.94 (IO_L25P_4); also elsewhere on the board
SNES_A0: U201.119 (IO_L22P_3); also elsewhere on the board
SNES_A1: U201.122 (IO_L23P_3/VREF_3); also elsewhere on the board
SNES_A2: U201.124 (IO_L24P_3); also elsewhere on the board
SNES_A3: U201.126 (IO_L39P_3); also elsewhere on the board
SNES_A4: U201.130 (IO_L40P_3); also elsewhere on the board
SNES_A5: U201.132 (IO_L40P_2/VREF_2); also elsewhere on the board
SNES_A6: U201.135 (IO_L39P_2); also elsewhere on the board
SNES_A7: U201.138 (IO_L24P_2); also elsewhere on the board
SNES_A8: U201.140 (IO_L23P_2); also elsewhere on the board
SNES_A9: U201.143 (IO_L22P_2); also elsewhere on the board
SNES_A10: U201.146 (IO_L21P_2); also elsewhere on the board
SNES_A11: U201.148 (IO_L20P_2); also elsewhere on the board
SNES_A12: U201.147 (IO-L21N_2); also elsewhere on the board
SNES_A13: U201.144 (IO_L22N_2); also elsewhere on the board
SNES_A14: U201.141 (IO_L23N_2/VREF_2); also elsewhere on the board
SNES_A15: U201.139 (IO_L24N_2); also elsewhere on the board
SNES_A16: U201.137 (IO_L39N_2); also elsewhere on the board
SNES_A17: U201.133 (IO_L40N_2); also elsewhere on the board
SNES_A18: U201.131 (IO_L40N_3/VREF_3); also elsewhere on the board
SNES_A19: U201.128 (IO_L39N_3); also elsewhere on the board
SNES_A20: U201.125 (IO_L24N_3); also elsewhere on the board
SNES_A21: U201.123 (IO_L23N_3); also elsewhere on the board
SNES_A22: U201.120 (IO_L22N_3); also elsewhere on the board
SNES_A23: U201.117 (IO_L21N_3); also elsewhere on the board
SNES_CPU_CLK: U201.95 (IO_L25N_4); also elsewhere on the board
SNES_D0: U201.107 (IO_L01N_3/VRP_3); also elsewhere on the board
SNES_D1: U201.102 (IO/VREF_4); also elsewhere on the board
SNES_D2: U201.100 (IO_L01P_4/VRN_4); also elsewhere on the board
SNES_D3: U201.96 (IO/VREF_4); also elsewhere on the board
SNES_D4: U201.108 (IO_L17P_3/VREF_3); also elsewhere on the board
SNES_D5: U201.106 (IO_L01P_3/VRN_3); also elsewhere on the board
SNES_D6: U201.101 (IO_L01N_4/VRP_4); also elsewhere on the board
SNES_D7: U201.97 (IO); also elsewhere on the board
SNES_IRQ_EN: U201.114 (IO_L20P_3); also elsewhere on the board
SNES_PA0: U201.90 (IO_L27P_4/D1); also elsewhere on the board
SNES_PA1: U201.93 (IO); also elsewhere on the board
SNES_PA2: U201.86 (IO_L30P_4/D3); also elsewhere on the board
SNES_PA3: U201.87 (IO_L30N_4/D2); also elsewhere on the board
SNES_PA4: U201.81 (IO_L31P_4/DOUT/BUSY); also elsewhere on the board
SNES_PA5: U201.85 (IO/VREF_4); also elsewhere on the board
SNES_PA6: U201.152 (IO_L19N_2); also elsewhere on the board
SNES_PA7: U201.154 (IO/VREF_2); also elsewhere on the board
SNES_REFRESH: U201.155 (IO_L01P_2/VRN_2); also elsewhere on the board
SNES_SYS_CLK: U201.180 (IO_L32P_1/GCLK4); also elsewhere on the board

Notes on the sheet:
FPGA
SNES A+B bus
70ns PSRAM bus
45ns SRAM bus
SD bus; shared with MCU
SPI (MCU interface)
DAC
JTAG

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
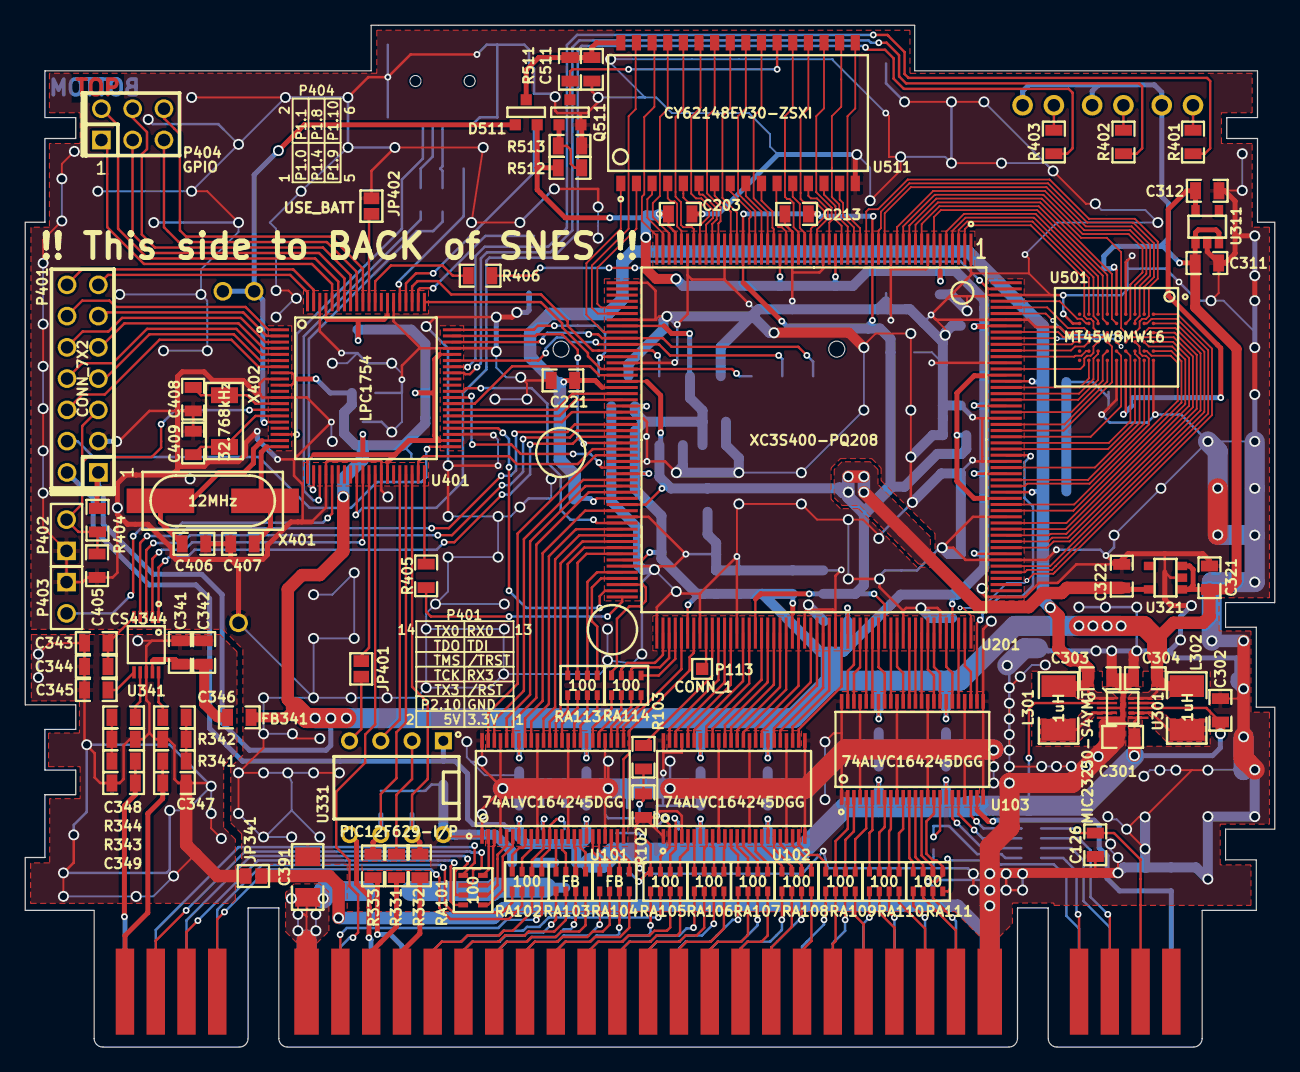
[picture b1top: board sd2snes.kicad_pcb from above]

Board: 2 copper layers, 101.5 x 83.0 mm, 153 parts (0 on the bottom side), 326 nets.

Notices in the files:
pcb/kicad/RevF/sd2snes.kicad_pcb:
©2009 - 2014 ikari_01
